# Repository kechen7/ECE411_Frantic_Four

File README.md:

# ECE411_Frantic_Four

Go here for next tasks!
https://trello.com/b/G3a4vdUh/ece411-practicum-project

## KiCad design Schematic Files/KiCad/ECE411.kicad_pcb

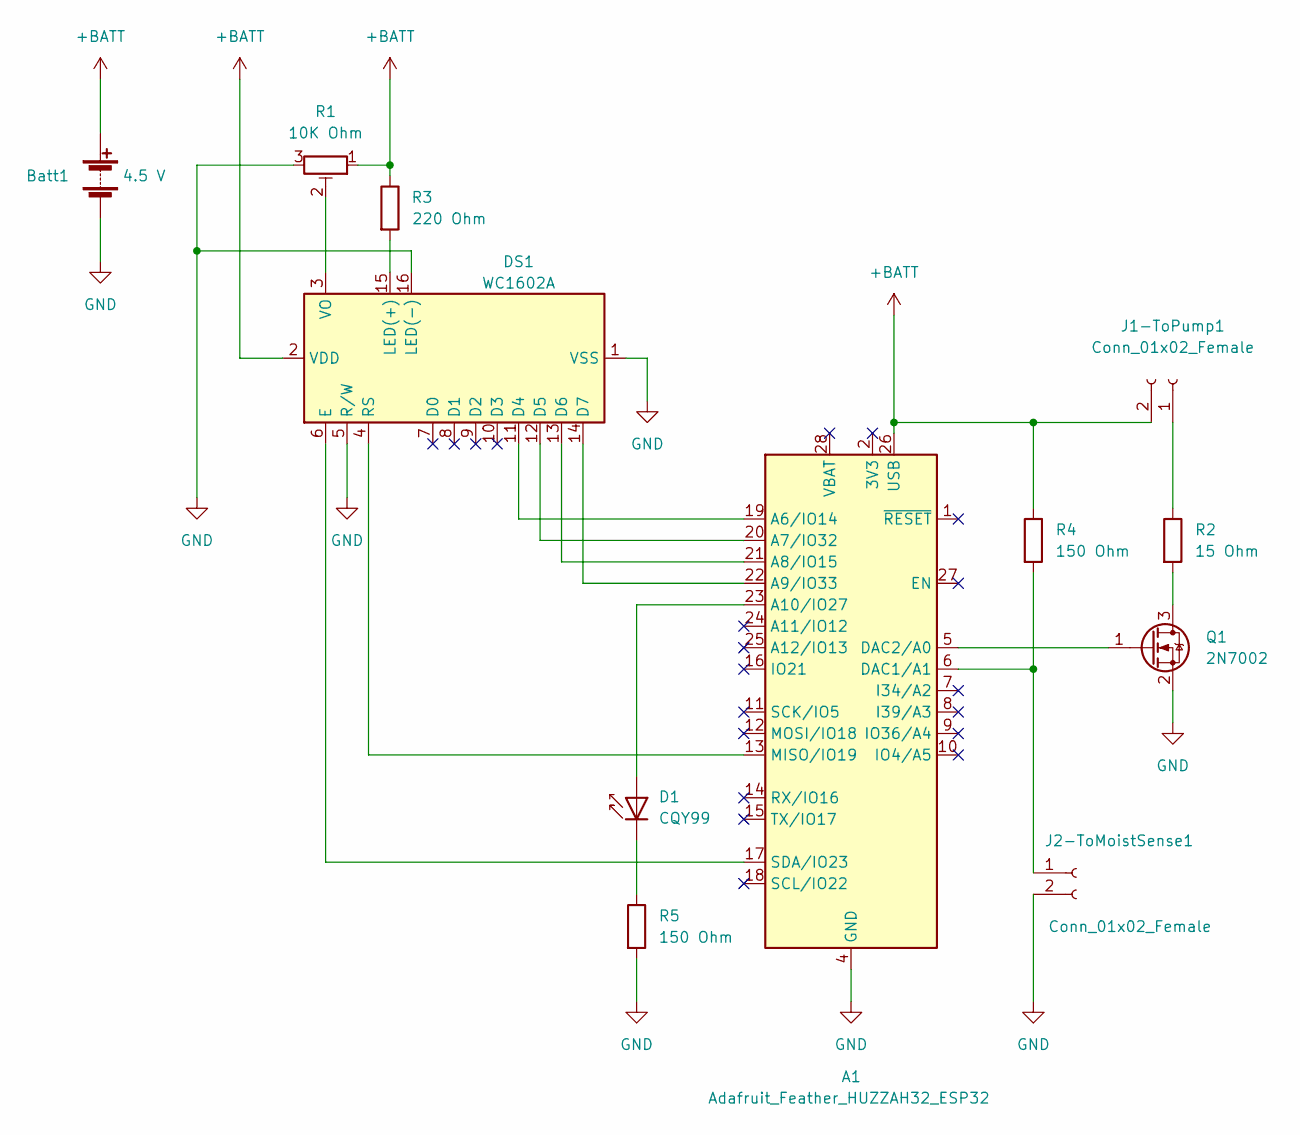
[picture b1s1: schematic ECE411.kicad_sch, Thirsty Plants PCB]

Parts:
A1: Adafruit_Feather_HUZZAH32_ESP32; Adafruit_Feather
Batt1: 4.5 V; TestPoint_2Pads_Pitch5.08mm_Drill1.3mm
D1: CQY99; LED_D5.0mm_IRGrey
DS1: WC1602A
J1-ToPump1, J2-ToMoistSense1: Conn_01x02_Female; TestPoint_2Pads_Pitch5.08mm_Drill1.3mm
Q1: 2N7002; SOT-23
R1: 10K Ohm; Potentiometer_Bourns_TC33X_Vertical
R2: 15 Ohm; R_1206_3216Metric
R3: 220 Ohm; R_1206_3216Metric
R4, R5: 150 Ohm; R_1206_3216Metric

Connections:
+BATT: A1.26 (USB), Batt1.1 (+), DS1.2 (VDD), J1-ToPump1.2, R1.1, R3.1, R4.1
GND: A1.4 (GND), Batt1.2 (-), DS1.1 (VSS), DS1.5 (R/W), DS1.16 (LED(-)), J2-ToMoistSense1.2, Q1.2 (S), R1.3, R5.2
unnamed: A1.5 (DAC2/A0), Q1.1 (G)
unnamed: A1.6 (DAC1/A1), J2-ToMoistSense1.1, R4.2
unnamed: A1.13 (MISO/IO19), DS1.4 (RS)
unnamed: A1.17 (SDA/IO23), DS1.6 (E)
unnamed: A1.19 (A6/IO14), DS1.11 (D4)
unnamed: A1.20 (A7/IO32), DS1.12 (D5)
unnamed: A1.21 (A8/IO15), DS1.13 (D6)
unnamed: A1.22 (A9/IO33), DS1.14 (D7)
unnamed: A1.23 (A10/IO27), D1.2 (A)
unnamed: D1.1 (K), R5.1
unnamed: DS1.3 (VO), R1.2
unnamed: DS1.15 (LED(+)), R3.2
unnamed: J1-ToPump1.1, R2.1
unnamed: Q1.3 (D), R2.2

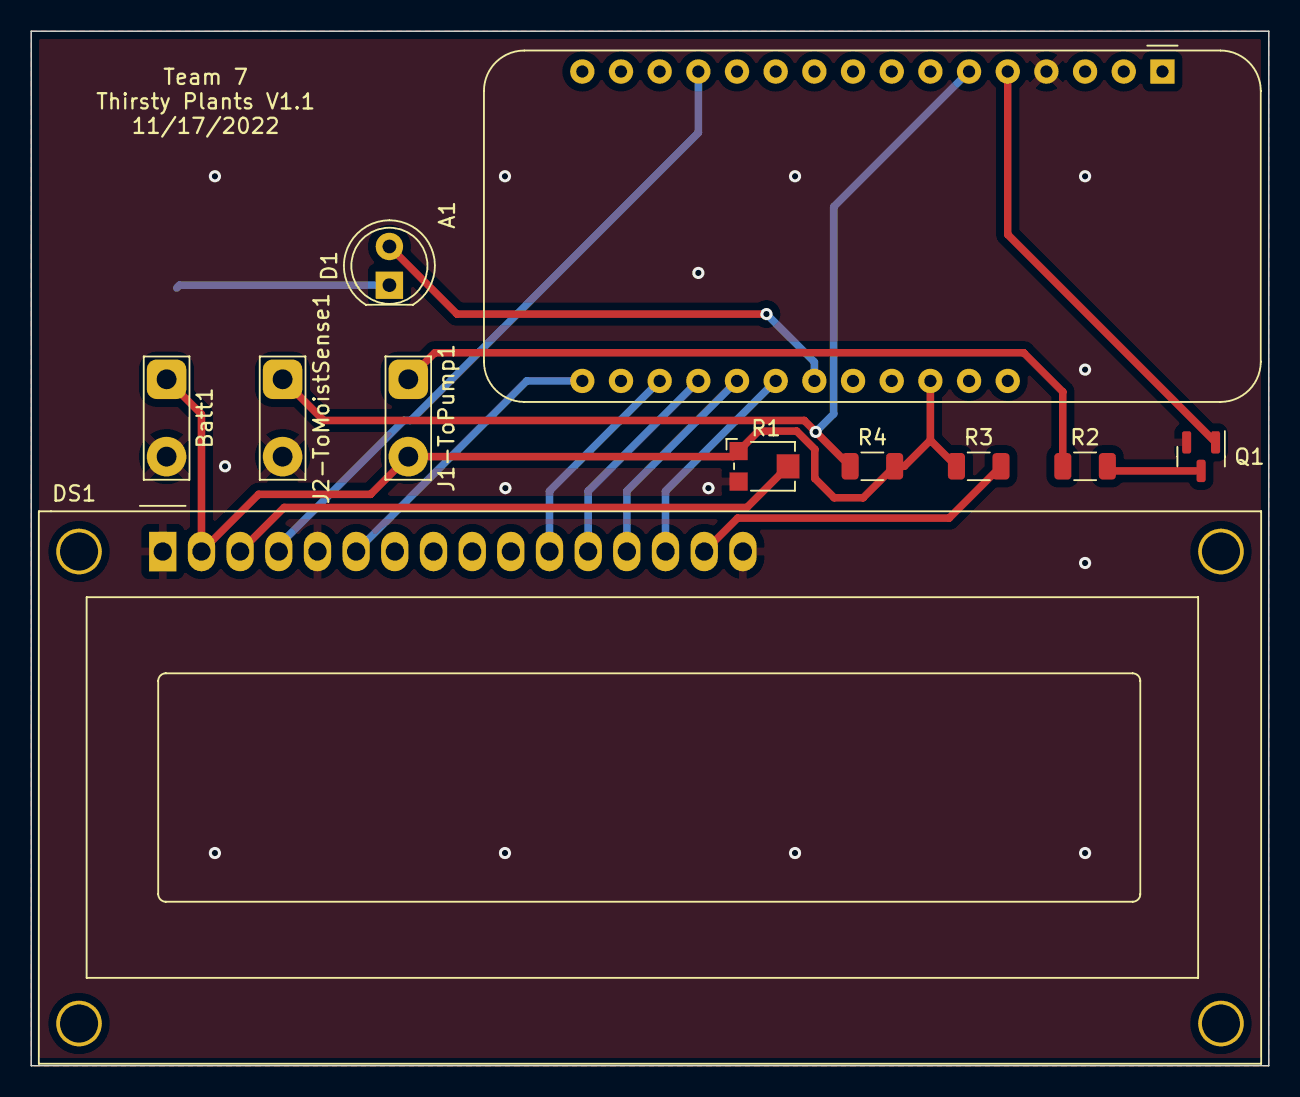
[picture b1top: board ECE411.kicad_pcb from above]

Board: 2 copper layers, 81.3 x 67.9 mm, 12 parts (1 on the bottom side), 16 nets.

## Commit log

2022-10-27 Actions
2022-11-02 Gantt Chart for Team Schedule
2022-11-02 starter code
2022-11-02 Breadboard Prototype
    The prototype we have built is still in its early development stages. We have connected all of the peripherals to the processor as needed. The initial setup involves connecting the processor to the I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
    In terms of materials that were delivered. All materials are present and good for use. The only thing that might be of any concern would be the g
2022-11-04 Create Place here
2022-11-04 Create start
2022-11-04 Rename ECE411.kicad_pcb to Schematic Files/ECE411.kicad_pcb
2022-11-04 Rename Schematic Files/ECE411.kicad_pcb to Schematic Files/KiCad/ECE411.kicad_pcb
2022-11-04 Rename ECE411.kicad_prl to Schematic Files/KiCad/ECE411.kicad_prl
2022-11-04 Rename ECE411.kicad_sch to Schematic Files/KiCad/ECE411.kicad_sch
2022-11-04 Rename ECE411.kicad_pro to Schematic Files/KiCad/ECE411.kicad_pro
2022-11-04 Rename sketch_enable_MOT.ino to code/sketch_enable_MOT.ino
2022-11-08 BOM
    Version 1
2022-11-10 Functional Decomposition
    Level 0 and 1
2022-11-15 post design review
2022-12-01 Test Plans for Thirsty Plants
    PDF includes 3 test plans. Upload a filled out test plan here when complete.
2022-12-02 Add files via upload
    code with lcd, pump and sensor
2022-12-02 Add files via upload
    added the led
2022-12-04 Add files via upload
    testing on uno using a relay
